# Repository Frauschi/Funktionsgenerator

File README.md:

# Funktionsgenerator

Dieses Repository beinhaltet alle relevaten Dateien für den Bau eines Funktionsgenerators. Dieser ist
im Rahmen einer Projektarbeit and der *Ostbayerischen Technischen Hochschule Regensburg* enstanden.

### Specs des Funktionsgenerators

- Zwei unabhängige Ausgangskanäle
- Signalformen: Sinus, Recheck (einstellbarer Duty-Cycle), Dreieck, Sägezahn (ansteigend und abfallend)
- Frequenz: 1Hz – 10MHz
- Ausgangsspannung: -10V – +10V 
- Signal-Offset: -5V – +5V
- Signal-Phase -180° – +180°

### Entwickler

- Manuel Dentgen
- Tobias Frauenschläger
- Thomas Taugenbeck

### Verzeichnisstruktur

- `Bilder` 
	
	Dieses Verzeichnis beinhaltet sowohl Bilder vom Gerät selbst (3D Modell und tatsächliches Gerät) als 
	auch Bilder von den erzeugten Signalen.
	
- `Dokumentation` 

	Dieser Ordner enthält zum einen die Projektdokumentation und zum anderen eine Bedienungsanleitung für den 
	fertigen Funktionsgenerator.
	
- `Hardware` 

	Hier sind alle Dateien für die drei entwickelten Platinen abgelegt (Schaltplan und Layout).
	
- `Software` 
	
	In diesem Verzeichnis ist die Firmware für den Mikrocontroller zu finden, der das ganze Gerät steuert.

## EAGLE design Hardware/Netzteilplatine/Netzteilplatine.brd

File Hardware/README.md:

# Hardware Funktionsgenerator

In diesem Verzeichnis ist die selbstentwickelte Hardware für den Funktionsgenerator zu finden, 
aufgeteilt auf die drei Platinen `Frontpanel`, `Hauptplatine` und `Netzteilplatine`. Im jeweiligen Ordner 
sind die Schaltplan- und Layout-Dateien abgelegt, wobei diese mit dem Programm 
[Eagle](https://www.autodesk.com/products/eagle/overview) in Version 7.7 erstellt wurden. Die Schaltpläne
sind zudem als PDF verfügbar.

## Dokumentation

Die Dokumentation der Hardware ist in der Projektdokumentation im Verzeichnis `Dokumentation` zu finden.

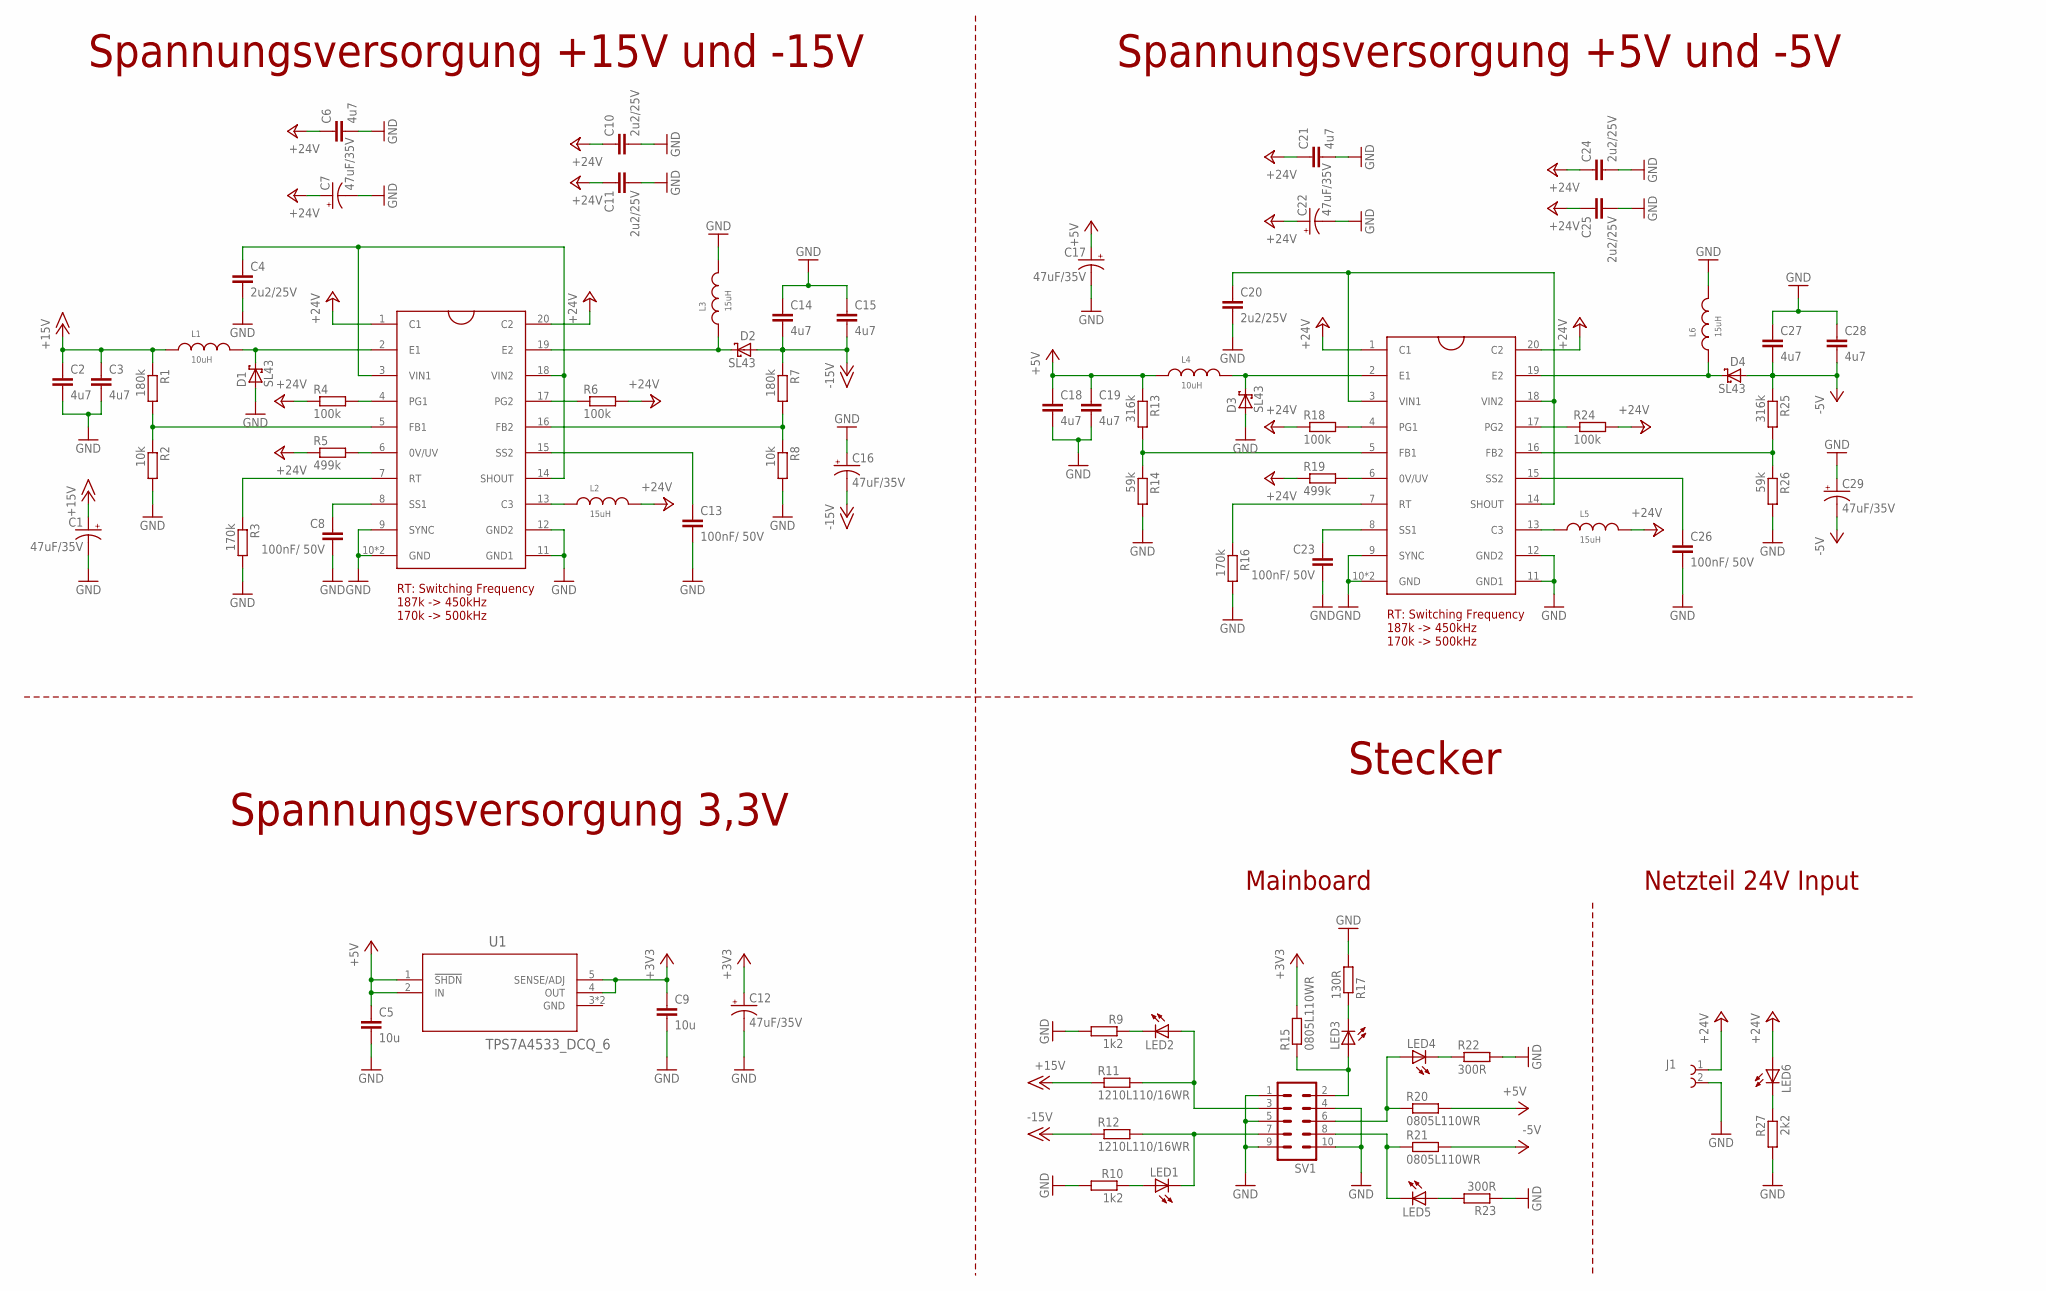
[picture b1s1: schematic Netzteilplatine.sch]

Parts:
C1, C7, C12, C16, C17, C22, C29: 47uF/35V; PANASONIC_D
C2, C3, C6, C14, C15, C18, C19, C21, C27, C28: 4u7; C1210
C4, C10, C11, C20, C24, C25: 2u2/25V; C1210
C5, C9: 10u; C0805
C8, C13, C23, C26: 100nF/ 50V; C0603
D1, D2, D3, D4: SL43; SMC
J1: 691137810002
L1, L4: 10uH; WE-PD_7332-7345_PLASTIC_BASE
L2, L3, L5, L6: 15uH; WE-PD2SR_7850
LED1, LED2, LED3, LED4, LED5, LED6: LEDCHIPLED_0603; CHIPLED_0603
R1, R7: 180k; R0603
R2, R8: 10k; R0603
R3, R16: 170k; R0603
R4, R6, R18, R24: 100k; R0603
R5, R19: 499k; R0603
R9, R10: 1k2; R0603
R11, R12: 1210L110/16WR; R1206
R13, R25: 316k; R0603
R14, R26: 59k; R0603
R15, R20, R21: 0805L110WR; R0805
R17: 130R; R0603
R22, R23: 300R; R0603
R27: 2k2; R0603
SV1: ML10
U1: TPS7A4533_DCQ_6; DCQ6
U2, U3: LT8471; TSSOP20

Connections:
+3V3: C9.1, C12.+, R15.2, U1.4 (OUT), U1.5 (SENSE/ADJ)
+5V: C5.1, C17.+, C18.1, C19.1, L4.1, R13.1, R20.2, U1.1 (!SHDN), U1.2 (IN)
+15V: C1.+, C2.1, C3.1, L1.1, R1.1, R11.1
+24V: C6.1, C7.+, C10.1, C11.1, C21.1, C22.+, C24.1, C25.1, J1.1, L2.2, L5.2, LED6.A, R4.1, R5.1, R6.2, R18.1, R19.1, R24.2, U2.1 (C1), U2.20 (C2), U3.1 (C1), U3.20 (C2)
-5V: C27.2, C28.2, C29.-, D4.A, R21.2, R25.1
-15V: C14.2, C15.2, C16.-, D2.A, R7.1, R12.1
GND: C1.-, C2.2, C3.2, C4.2, C5.2, C6.2, C7.-, C8.2, C9.2, C10.2, C11.2, C12.-, C13.2, C14.1, C15.1, C16.+, C17.-, C18.2, C19.2, C20.2, C21.2, C22.-, C23.2, C24.2, C25.2, C26.2, C27.1, C28.1, C29.+, D1.A, D3.A, J1.2, L3.2, L6.2, R2.2, R3.2, R8.2, R9.2, R10.2, R14.2, R16.2, R17.2, R22.2, R23.1, R26.2, R27.2, SV1.1, SV1.4, SV1.5, SV1.9, SV1.10, U1.3 (GND), U1.P$1 (GND), U2.9 (SYNC), U2.10 (GND), U2.11 (GND1), U2.12 (GND2), U2.P$1 (GND), U3.9 (SYNC), U3.10 (GND), U3.11 (GND1), U3.12 (GND2), U3.P$1 (GND)
unnamed: C4.1, U2.3 (VIN1), U2.14 (SHOUT), U2.18 (VIN2)
unnamed: R7.2, R8.1, U2.16 (FB2)
unnamed: R1.2, R2.1, U2.5 (FB1)
unnamed: R5.2, U2.6 (0V/UV)
unnamed: C20.1, U3.3 (VIN1), U3.14 (SHOUT), U3.18 (VIN2)
unnamed: C8.1, U2.8 (SS1)
unnamed: R19.2, U3.6 (0V/UV)
unnamed: C13.1, U2.15 (SS2)
unnamed: C23.1, U3.8 (SS1)
unnamed: C26.1, U3.15 (SS2)
unnamed: R25.2, R26.1, U3.16 (FB2)
unnamed: R13.2, R14.1, U3.5 (FB1)
unnamed: R3.1, U2.7 (RT)
unnamed: R16.1, U3.7 (RT)
unnamed: D1.C, L1.2, U2.2 (E1)
unnamed: D2.C, L3.1, U2.19 (E2)
unnamed: L2.1, U2.13 (C3)
unnamed: D3.C, L4.2, U3.2 (E1)
unnamed: R6.1, U2.17 (PG2)
unnamed: R4.2, U2.4 (PG1)
unnamed: D4.C, L6.1, U3.19 (E2)
unnamed: L5.1, U3.13 (C3)
unnamed: R24.1, U3.17 (PG2)
unnamed: R18.2, U3.4 (PG1)
unnamed: LED3.A, R15.1, SV1.2
unnamed: LED4.A, R20.1, SV1.6
unnamed: LED4.C, R22.1
unnamed: LED1.C, R12.2, SV1.7
unnamed: LED5.C, R21.1, SV1.8
unnamed: LED5.A, R23.2
unnamed: LED2.A, R11.2, SV1.3
unnamed: LED3.C, R17.1
unnamed: LED2.C, R9.1
unnamed: LED1.A, R10.1
unnamed: LED6.C, R27.1

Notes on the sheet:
Spannungsversorgung +15V und -15V
Spannungsversorgung 3,3V
RT: Switching Frequency 187k -> 450kHz 170k -> 500kHz
Spannungsversorgung +5V und -5V
Stecker
Mainboard
Netzteil 24V Input

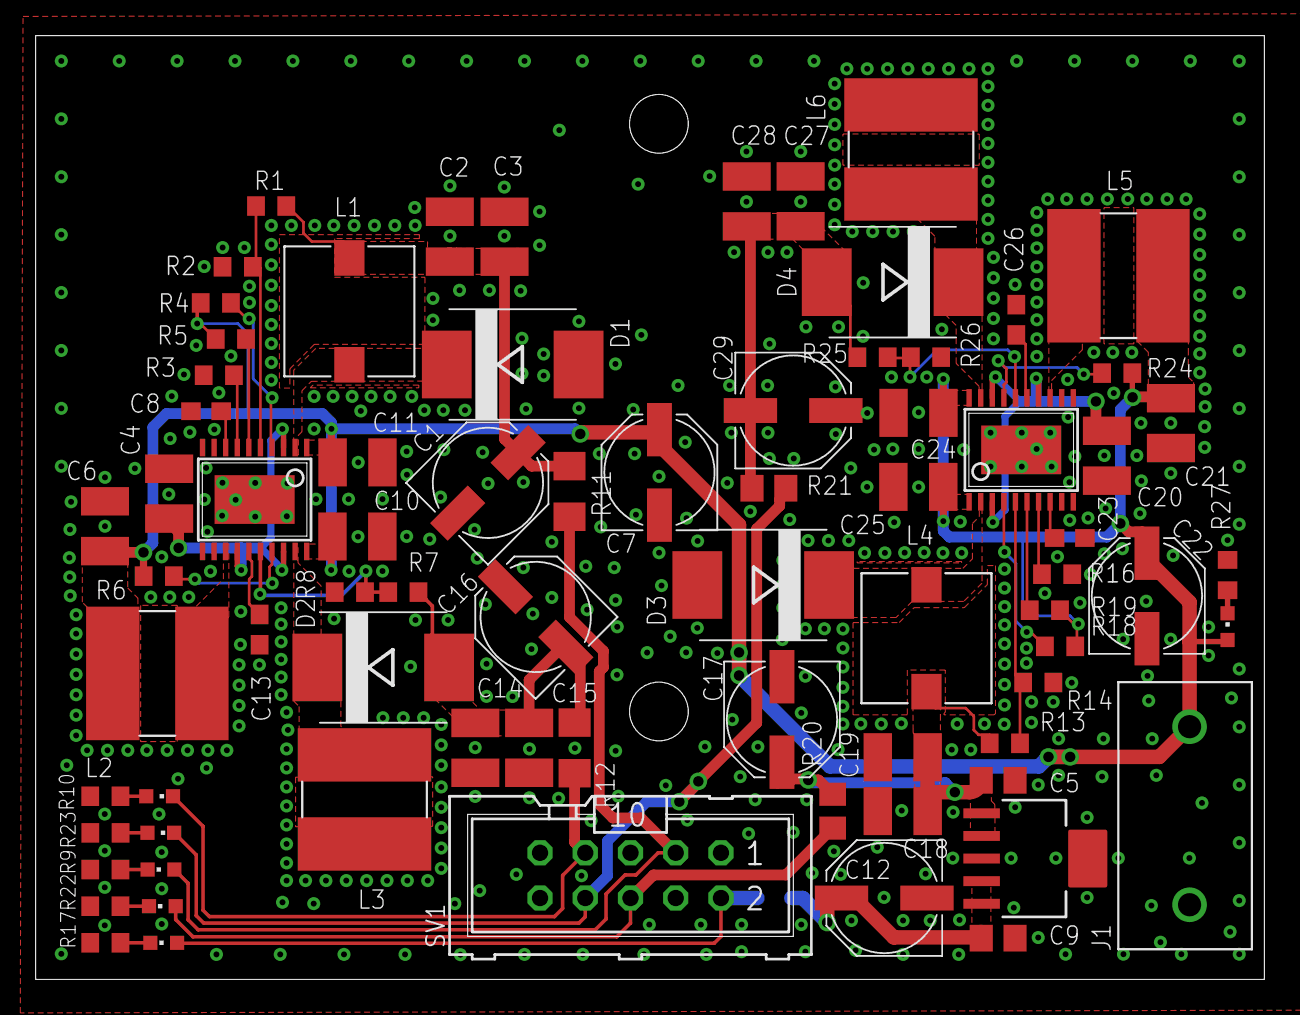
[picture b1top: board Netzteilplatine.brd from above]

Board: 2 copper layers, 69.0 x 53.0 mm, 77 parts (1 on the bottom side), 42 nets.

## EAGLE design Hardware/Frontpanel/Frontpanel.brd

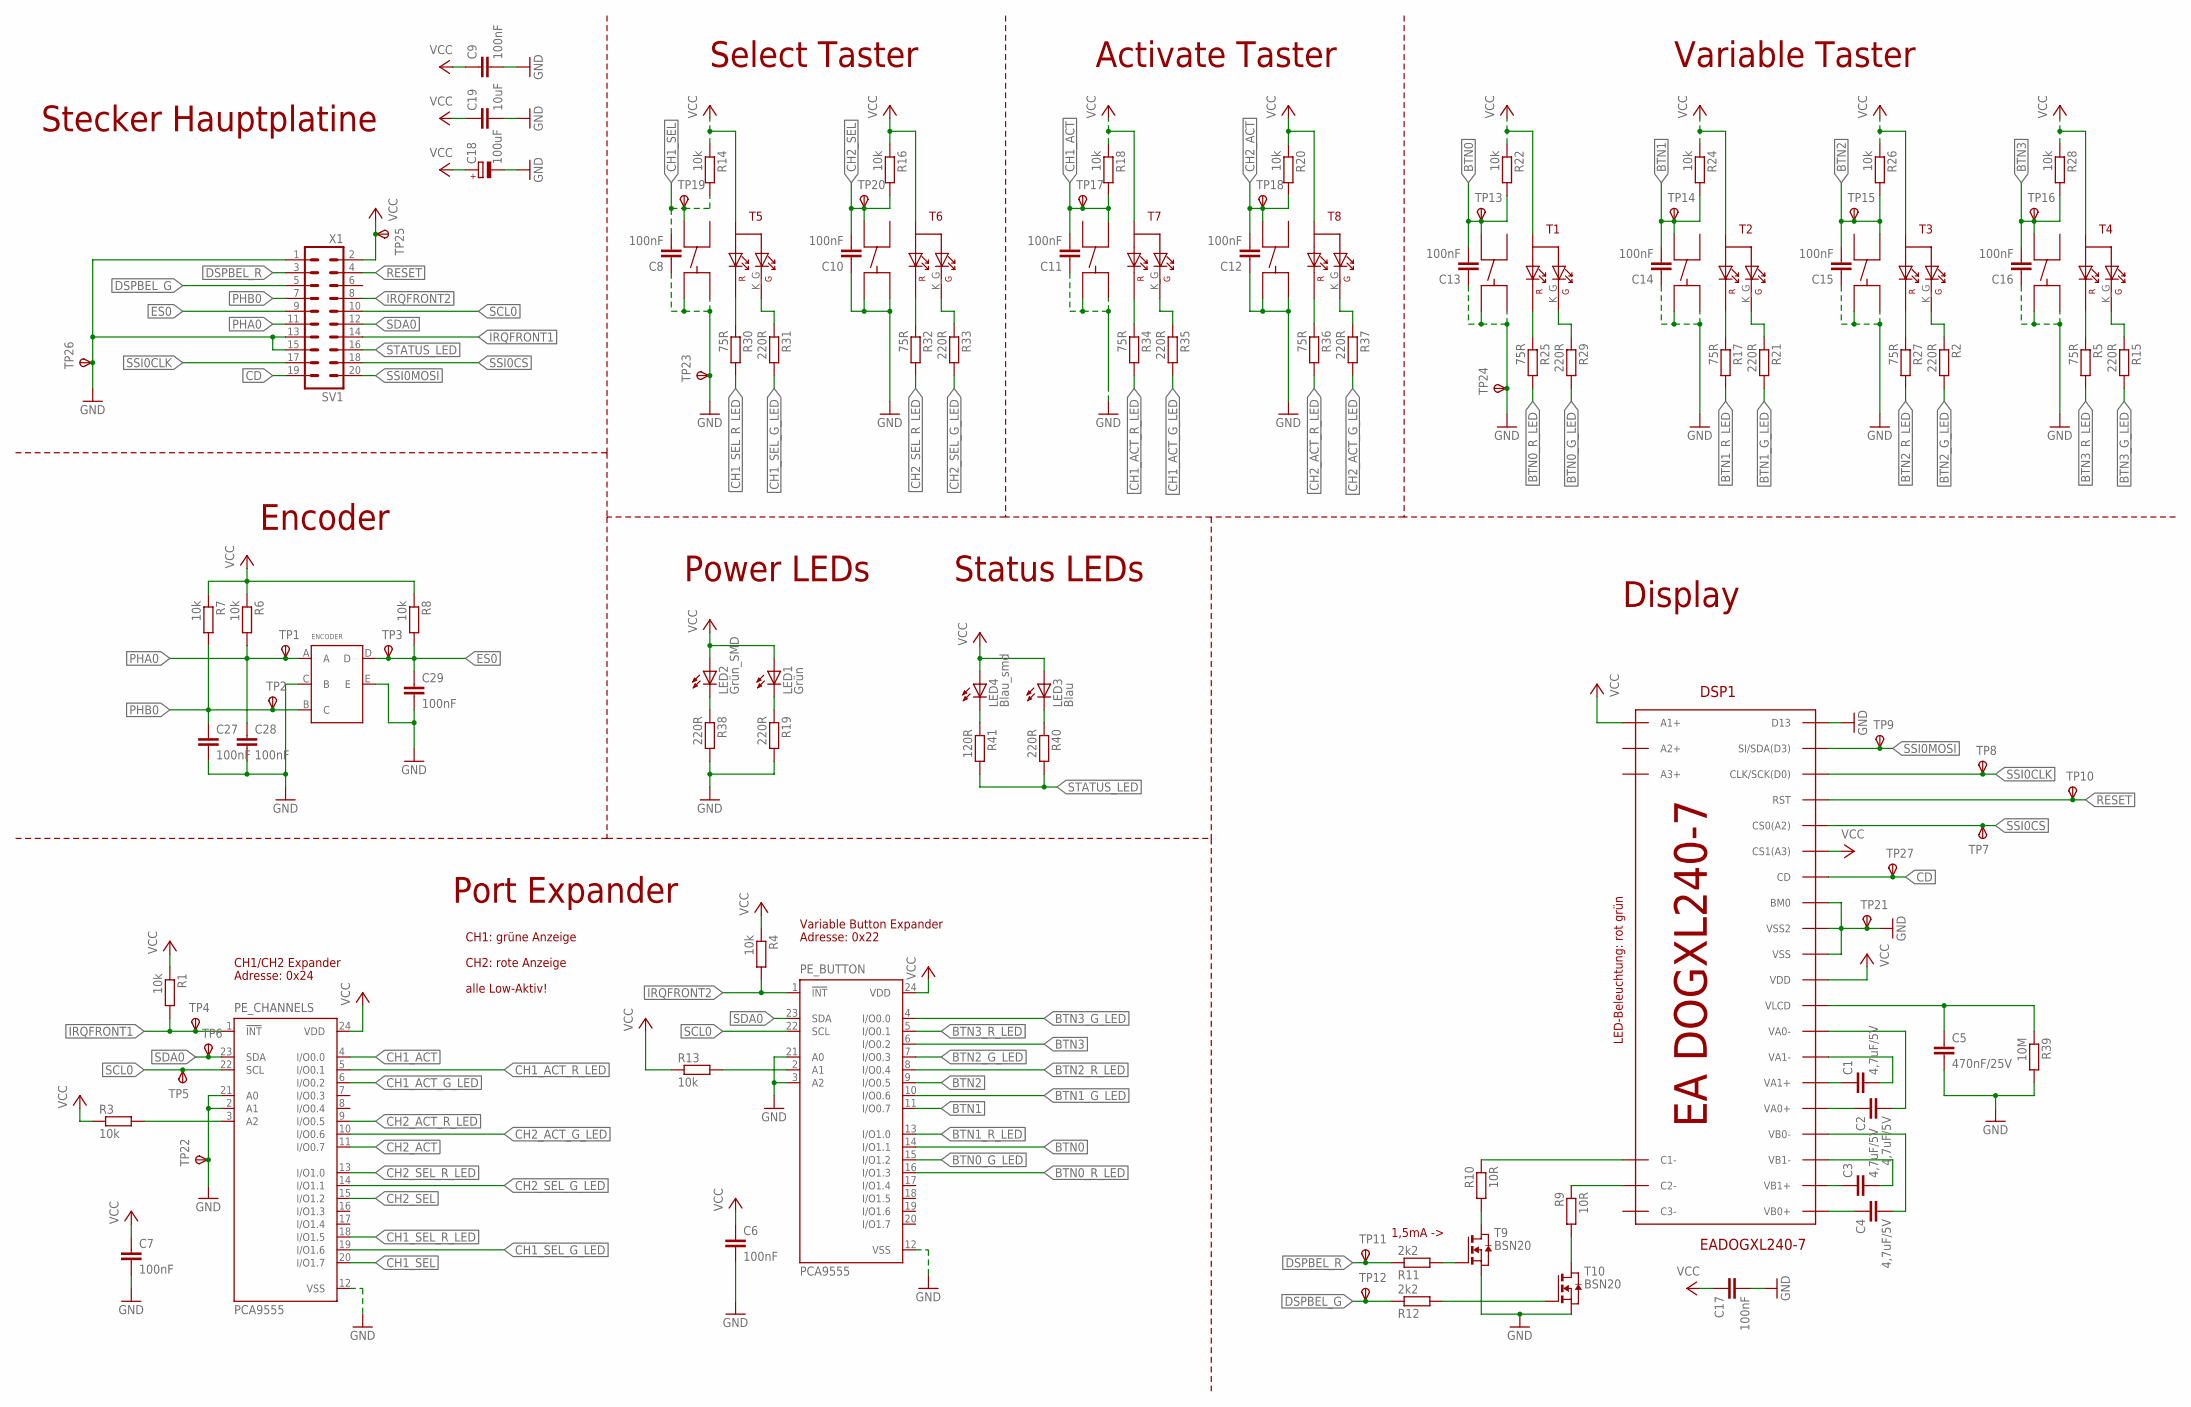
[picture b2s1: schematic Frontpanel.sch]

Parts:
C1, C2, C3, C4: 4,7uF/5V; C0805
C5: 470nF/25V; C0603
C6, C7, C8, C9, C10, C11, C12, C13, C14, C15, C16, C17, C27, C28, C29: 100nF; C0603
C18: 100uF; CT7343
C19: 10uF; C0805
DSP1: EADOGXL240-7
ENCODER: ENCODER
LED1: Grün; LED5MM
LED2: Grün_SMD; CHIP-LED0603
LED3: Blau; LED5MM
LED4: Blau_smd; CHIP-LED0603
PE_BUTTON: PCA9555; SSOP24_DBQ
PE_CHANNELS: PCA9555; SSOP24_DBQ
R1, R3, R4, R6, R7, R8, R13, R14, R16, R18, R20, R22, R24, R26, R28: 10k; R0603
R2, R15, R19, R21, R29, R31, R33, R35, R37, R38, R40: 220R; R0603
R5, R17, R25, R27, R30, R32, R34, R36: 75R; R0603
R9, R10: 10R; M1206
R11, R12: 2k2; R0603
R39: 10M; R0603
R41: 120R; R0603
SV1: X1; ML20
T1, T2, T3, T4, T5, T6, T7, T8: TASTER_2FSH9_E_BEL; TASTER_3FSH9_SMD_E
T9, T10: BSN20; SOT-23
TP1, TP2, TP3, TP4, TP5, TP6, TP7, TP8, TP9, TP10, TP11, TP12, TP13, TP14, TP15, TP16, TP17, TP18, TP19, TP20, TP21, TP22, TP23, TP24, TP25, TP26, TP27: TPSB1,27; B1,27

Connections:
BTN0: C13.2, PE_BUTTON.14 (I/O1.1), R22.2, T1.13, TP13.TP
BTN0_G_LED: PE_BUTTON.15 (I/O1.2), R29.2
BTN0_R_LED: PE_BUTTON.16 (I/O1.3), R25.2
BTN1: C14.2, PE_BUTTON.11 (I/O0.7), R24.2, T2.13, TP14.TP
BTN1_G_LED: PE_BUTTON.10 (I/O0.6), R21.2
BTN1_R_LED: PE_BUTTON.13 (I/O1.0), R17.2
BTN2: C15.2, PE_BUTTON.9 (I/O0.5), R26.2, T3.23, TP15.TP
BTN2_G_LED: PE_BUTTON.7 (I/O0.3), R2.2
BTN2_R_LED: PE_BUTTON.8 (I/O0.4), R27.2
BTN3: C16.2, PE_BUTTON.6 (I/O0.2), R28.2, T4.13, TP16.TP
BTN3_G_LED: PE_BUTTON.4 (I/O0.0), R15.2
BTN3_R_LED: PE_BUTTON.5 (I/O0.1), R5.2
CD: DSP1.CD, SV1.19, TP27.TP
CH1_ACT: C11.2, PE_CHANNELS.4 (I/O0.0), R18.2, T7.23, TP17.TP
CH1_ACT_G_LED: PE_CHANNELS.6 (I/O0.2), R35.2
CH1_ACT_R_LED: PE_CHANNELS.5 (I/O0.1), R34.2
CH1_SEL: C8.2, PE_CHANNELS.20 (I/O1.7), R14.2, T5.13, TP19.TP
CH1_SEL_G_LED: PE_CHANNELS.19 (I/O1.6), R31.2
CH1_SEL_R_LED: PE_CHANNELS.18 (I/O1.5), R30.2
CH2_ACT: C12.2, PE_CHANNELS.11 (I/O0.7), R20.2, T8.13, TP18.TP
CH2_ACT_G_LED: PE_CHANNELS.10 (I/O0.6), R37.2
CH2_ACT_R_LED: PE_CHANNELS.9 (I/O0.5), R36.2
CH2_SEL: C10.2, PE_CHANNELS.15 (I/O1.2), R16.2, T6.13, TP20.TP
CH2_SEL_G_LED: PE_CHANNELS.14 (I/O1.1), R33.2
CH2_SEL_R_LED: PE_CHANNELS.13 (I/O1.0), R32.2
DSPBEL_G: R12.1, SV1.5, TP12.TP
DSPBEL_R: R11.1, SV1.3, TP11.TP
ES0: C29.1, ENCODER.D, R8.2, SV1.9, TP3.TP
GND: C5.2, C6.2, C7.2, C8.1, C9.2, C10.1, C11.1, C12.1, C13.1, C14.1, C15.1, C16.1, C17.2, C18.-, C19.2, C27.2, C28.2, C29.2, DSP1.BM0, DSP1.D13, DSP1.VSS1 (VSS), DSP1.VSS2, ENCODER.C (B), ENCODER.E, PE_BUTTON.3 (A2), PE_BUTTON.12 (VSS), PE_BUTTON.21 (A0), PE_CHANNELS.2 (A1), PE_CHANNELS.12 (VSS), PE_CHANNELS.21 (A0), R19.2, R38.2, R39.2, SV1.1, SV1.13, SV1.15, T1.14, T1.24, T2.14, T2.24, T3.14, T3.24, T4.14, T4.24, T5.14, T5.24, T6.14, T6.24, T7.14, T7.24, T8.14, T8.24, T9.2 (S), T10.2 (S), TP21.TP, TP22.TP, TP23.TP, TP24.TP, TP26.TP
IRQFRONT1: PE_CHANNELS.1 (!INT), R1.2, SV1.14, TP4.TP
IRQFRONT2: PE_BUTTON.1 (!INT), R4.2, SV1.8
unnamed: PE_CHANNELS.3 (A2), R3.2
unnamed: R27.1, T3.K_R (KR)
unnamed: DSP1.C1-, R10.1
unnamed: PE_BUTTON.2 (A1), R13.2
unnamed: R11.2, T9.3 (G)
unnamed: DSP1.C2-, R9.1
unnamed: R12.2, T10.3 (G)
unnamed: R29.1, T1.K_G (KG)
unnamed: R25.1, T1.K_R (KR)
unnamed: R17.1, T2.K_R (KR)
unnamed: C1.1, DSP1.VA1+
unnamed: C2.1, DSP1.VA0+
unnamed: C3.1, DSP1.VB1+
unnamed: C4.1, DSP1.VB0+
unnamed: C3.2, DSP1.VB1-
unnamed: C4.2, DSP1.VB0-
unnamed: R9.2, T10.1 (D)
unnamed: R10.2, T9.1 (D)
unnamed: R21.1, T2.K_G (KG)
unnamed: R36.1, T8.K_R (KR)
unnamed: R2.1, T3.K_G (KG)
unnamed: R5.1, T4.K_R (KR)
unnamed: R15.1, T4.K_G (KG)
unnamed: R37.1, T8.K_G (KG)
unnamed: R34.1, T7.K_R (KR)
unnamed: R35.1, T7.K_G (KG)
unnamed: R32.1, T6.K_R (KR)
unnamed: R33.1, T6.K_G (KG)
unnamed: R30.1, T5.K_R (KR)
unnamed: R31.1, T5.K_G (KG)
unnamed: C1.2, DSP1.VA1-
unnamed: LED1.K (C), R19.1
unnamed: LED2.C, R38.1
unnamed: C2.2, DSP1.VA0-
unnamed: LED3.K (C), R40.1
unnamed: C5.1, DSP1.VLCD, R39.1
unnamed: LED4.C, R41.1
PHA0: C28.1, ENCODER.A, R6.2, SV1.11, TP1.TP
PHB0: C27.1, ENCODER.B (C), R7.2, SV1.7, TP2.TP
RESET: DSP1.RST, SV1.4, TP10.TP
SCL0: PE_BUTTON.22 (SCL), PE_CHANNELS.22 (SCL), SV1.10, TP5.TP
SDA0: PE_BUTTON.23 (SDA), PE_CHANNELS.23 (SDA), SV1.12, TP6.TP
SSI0CLK: DSP1.SCK(D0) (CLK/SCK(D0)), SV1.17, TP8.TP
SSI0CS: DSP1.CS0(A2), SV1.18, TP7.TP
SSI0MOSI: DSP1.SDA(D3) (SI/SDA(D3)), SV1.20, TP9.TP
STATUS_LED: R40.2, R41.2, SV1.16
VCC: C6.1, C7.1, C9.1, C17.1, C18.+, C19.1, DSP1.A1+, DSP1.CS1(A3), DSP1.VDD, LED1.A, LED2.A, LED3.A, LED4.A, PE_BUTTON.24 (VDD), PE_CHANNELS.24 (VDD), R1.1, R3.1, R4.1, R6.1, R7.1, R8.1, R13.1, R14.1, R16.1, R18.1, R20.1, R22.1, R24.1, R26.1, R28.1, SV1.2, T1.A, T2.A, T3.A, T4.A, T5.A, T6.A, T7.A, T8.A, TP25.TP

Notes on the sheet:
Stecker Hauptplatine
Adresse: 0x24
Encoder
Port Expander
Adresse: 0x22
CH1: grüne Anzeige
CH2: rote Anzeige
Variable Button Expander
CH1/CH2 Expander
alle Low-Aktiv!
Select Taster
Activate Taster
Variable Taster
Power LEDs
LED-Beleuchtung: rot grün
1,5mA ->
Status LEDs
Display

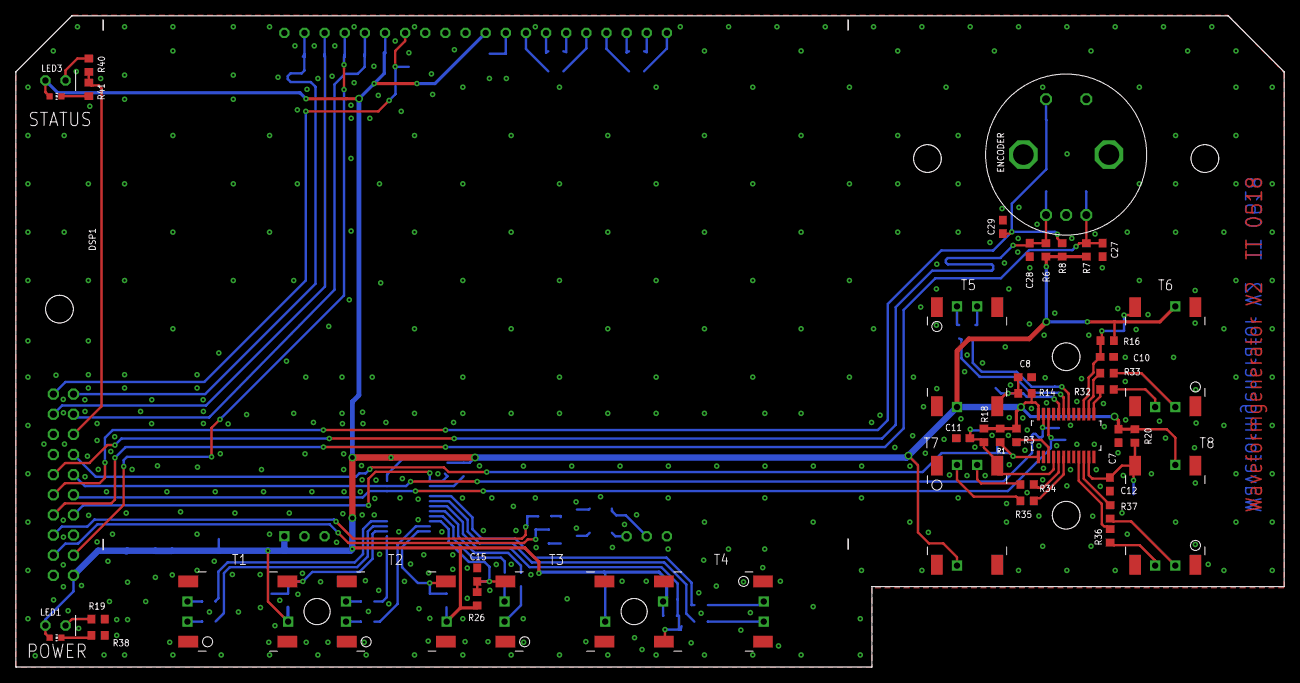
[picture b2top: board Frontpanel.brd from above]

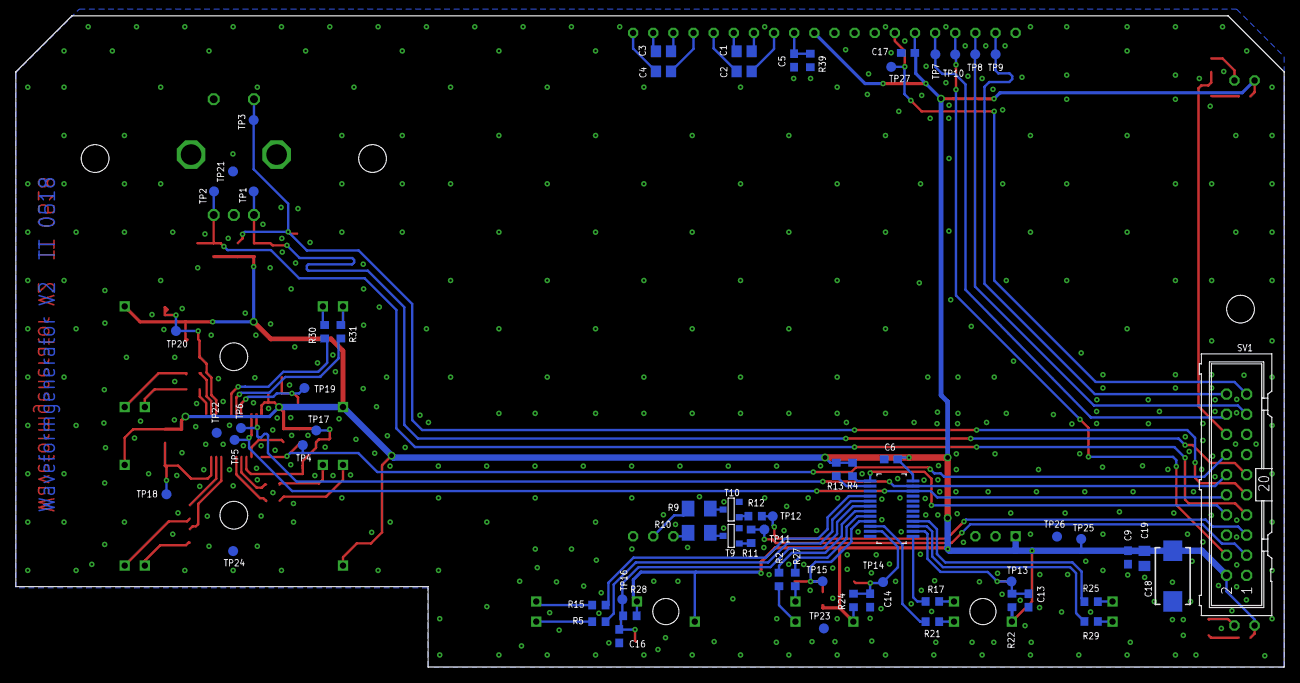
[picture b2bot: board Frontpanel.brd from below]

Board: 2 copper layers, 160.0 x 82.2 mm, 108 parts (64 on the bottom side), 78 nets.

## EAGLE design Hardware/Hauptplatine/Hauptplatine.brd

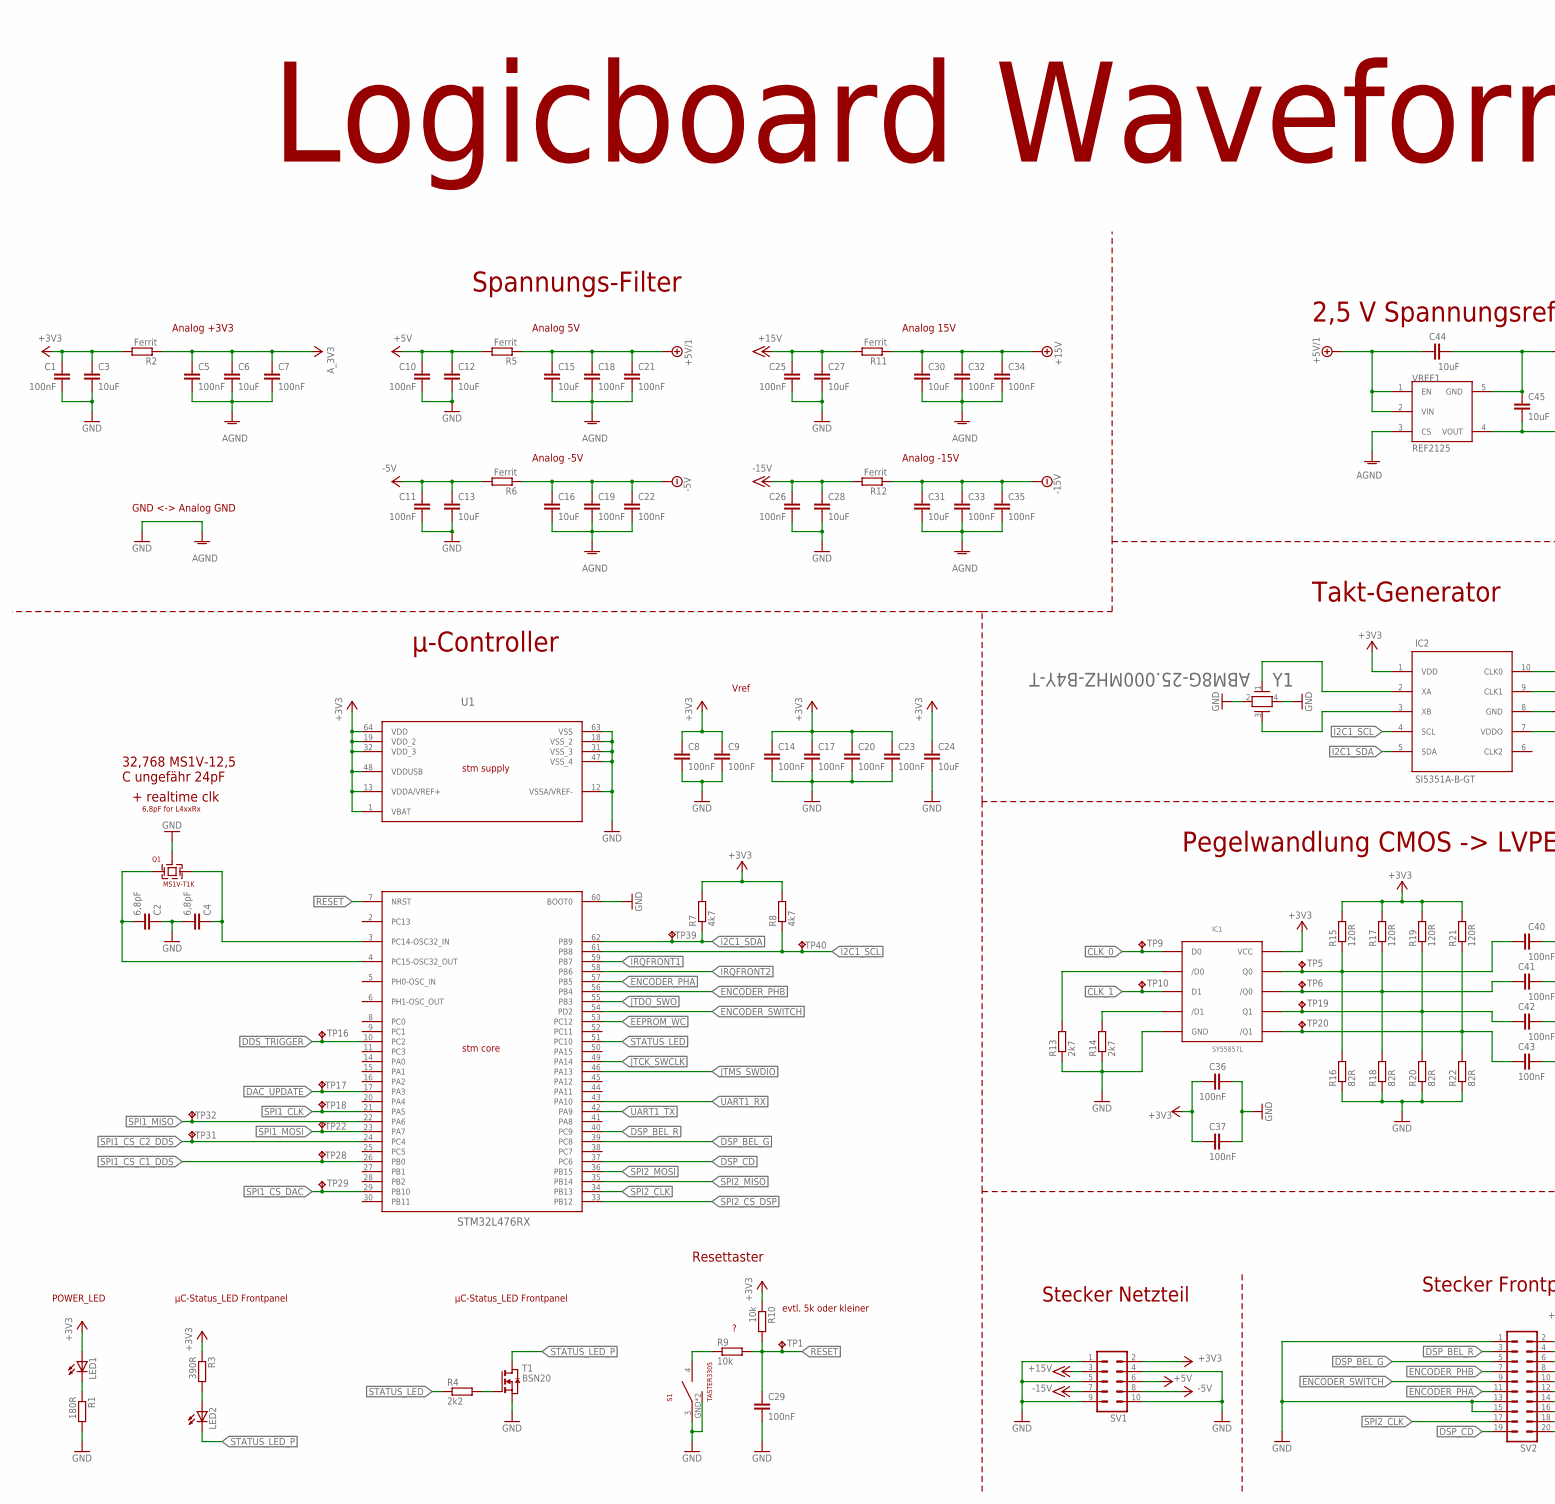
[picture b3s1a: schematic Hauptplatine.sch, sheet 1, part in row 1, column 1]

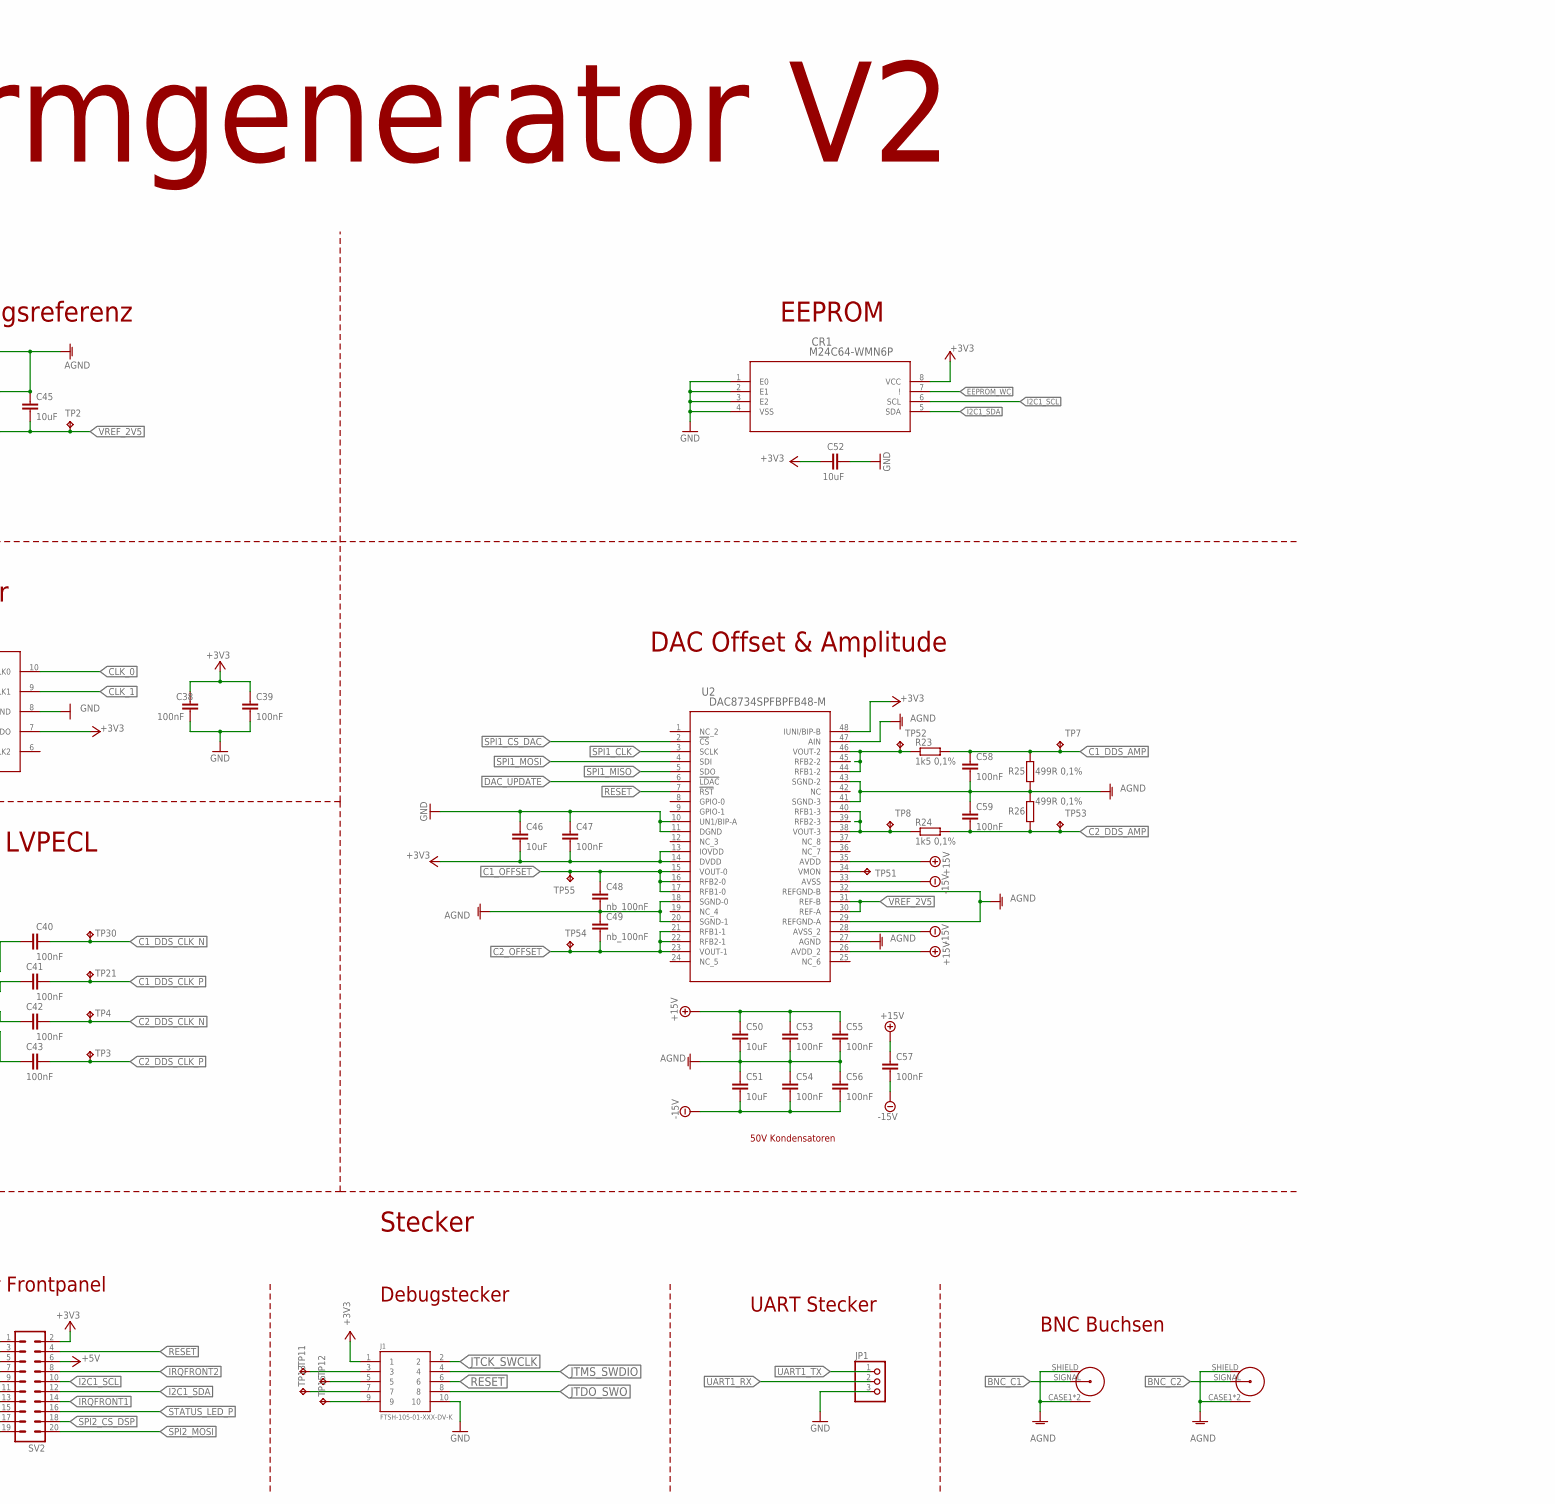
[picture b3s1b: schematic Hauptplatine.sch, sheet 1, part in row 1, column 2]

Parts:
C1, C5, C7, C8, C9, C10, C11, C14, C17, C18, C19, C20, C21, C22, C23, C25, C26, C29, C32, C33, C34, C35, C36, C37, C38, C39, C40, C41, C42, C43, C47, C53, C54, C55, C56, C57, C58, C59: 100nF; C0603
C2, C4: 6,8pF; C0603
C3, C6, C12, C13, C15, C16, C24, C27, C28, C30, C31, C44, C45, C46, C50, C51, C52: 10uF; C0603
C48, C49: nb_100nF; C0603
CR1: M24C64-WMN6P; SO-8
IC1: SY55857L; MSOP(K10-1)
IC2: SI5351A-B-GT; MSOP10
J1: FTSH-105-01-XXX-DV-K
JP1: PINHD-1X3; 1X03
LED1, LED2: LEDCHIPLED_0603; CHIPLED_0603
Q1: MS1V-T1K
R1: 180R; R0603
R2, R5, R6, R11, R12: Ferrit; R0603
R3: 390R; R0603
R4: 2k2; R0603
R7, R8: 4k7; R0603
R9, R10: 10k; R0603
R13, R14: 2k7; R0603
R15, R17, R19, R21: 120R; R0603
R16, R18, R20, R22: 82R; R0603
R23, R24: 1k5 0,1%; R0603
R25, R26: 499R 0,1%; R0603
S1: TASTER3305
SV1: ML10
SV2: ML20
T1: BSN20; SOT-23
TP1, TP2, TP3, TP4, TP5, TP6, TP7, TP8, TP9, TP10, TP11, TP12, TP13, TP15, TP16, TP17, TP18, TP19, TP20, TP21, TP22, TP28, TP29, TP30, TP31, TP32, TP39, TP40, TP51, TP52, TP53, TP54, TP55: TPB1,27; B1,27
U1: STM32L476RX; LQFP64-10X10MM
U2: DAC8734SPFBPFB48-M; PFB48-M
VREF1: REF2125; SOT23-5L
X1, X2: 740845_BNC
Y1: ABM8G-25.000MHZ-B4Y-T; CRYSTAL_ABM8G

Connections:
+3V3: C1.1, C3.1, C8.1, C9.1, C14.1, C17.1, C20.1, C23.1, C24.1, C36.1, C37.1, C38.1, C39.1, C46.2, C47.2, C52.1, CR1.8 (VCC), IC1.VCC, IC2.1 (VDD), IC2.7 (VDDO), J1.1, LED1.A, R2.2, R3.1, R7.2, R8.2, R10.1, R15.2, R17.2, R19.2, R21.2, SV1.2, SV2.2, U1.1 (VBAT), U1.13 (VDDA/VREF+), U1.19 (VDD_2), U1.32 (VDD_3), U1.48 (VDDUSB), U1.64 (VDD), U2.13 (IOVDD), U2.14 (DVDD), U2.48 (IUNI/BIP-B); also elsewhere on the board
+5V: C10.1, C12.1, R5.2, SV1.6, SV2.6
+5V/1: C15.1, C18.1, C21.1, C44.1, R5.1, VREF1.1 (EN), VREF1.2 (VIN); also elsewhere on the board
+15V: C25.1, C27.1, R11.2, SV1.3
+18V: C30.1, C32.1, C34.1, C50.1, C53.1, C55.1, C57.1, R11.1, U2.26 (AVDD_2), U2.35 (AVDD); also elsewhere on the board
-5V: C16.1, C19.1, C22.1, R6.1; also elsewhere on the board
-5V/D: C11.1, C13.1, R6.2, SV1.8
-15V: C26.1, C28.1, R12.2, SV1.7
-18V: C31.1, C33.1, C35.1, C51.2, C54.2, C56.2, C57.2, R12.1, U2.28 (AVSS_2), U2.33 (AVSS); also elsewhere on the board
ANALOG_3V3: C5.1, C6.1, C7.1, R2.1; also elsewhere on the board
BNC_C1: X1.SIGNAL; also elsewhere on the board
BNC_C2: X2.SIGNAL; also elsewhere on the board
C1_DDS_AMP: C58.1, R23.2, R25.2, TP7.TP; also elsewhere on the board
C1_DDS_CLK_N: C40.1, TP30.TP; also elsewhere on the board
C1_DDS_CLK_P: C41.1, TP21.TP; also elsewhere on the board
C1_OFFSET: C48.1, TP55.TP, U2.15 (VOUT-0), U2.16 (RFB2-0), U2.17 (RFB1-0); also elsewhere on the board
C2_DDS_AMP: C59.2, R24.2, R26.1, TP53.TP; also elsewhere on the board
C2_DDS_CLK_N: C42.1, TP4.TP; also elsewhere on the board
C2_DDS_CLK_P: C43.1, TP3.TP; also elsewhere on the board
C2_OFFSET: C49.2, TP54.TP, U2.21 (RFB1-1), U2.22 (RFB2-1), U2.23 (VOUT-1); also elsewhere on the board
CLK_0: IC1.D0, IC2.10 (CLK0), TP9.TP
CLK_1: IC1.D1, IC2.9 (CLK1), TP10.TP
DAC_UPDATE: TP17.TP, U1.17 (PA3), U2.6 (!LDAC)
DDS_TRIGGER: TP16.TP, U1.10 (PC2); also elsewhere on the board
DSP_BEL_G: SV2.5, U1.39 (PC8)
DSP_BEL_R: SV2.3, U1.40 (PC9)
DSP_CD: SV2.19, U1.37 (PC6)
EEPROM_WC: CR1.7 (!), U1.53 (PC12)
ENCODER_PHA: SV2.11, U1.57 (PB5)
ENCODER_PHB: SV2.7, U1.56 (PB4)
ENCODER_SWITCH: SV2.9, U1.54 (PD2)
GND: C1.2, C2.1, C3.2, C4.2, C5.2, C6.2, C7.2, C8.2, C9.2, C10.2, C11.2, C12.2, C13.2, C14.2, C15.2, C16.2, C17.2, C18.2, C19.2, C20.2, C21.2, C22.2, C23.2, C24.2, C25.2, C26.2, C27.2, C28.2, C29.2, C30.2, C31.2, C32.2, C33.2, C34.2, C35.2, C36.2, C37.2, C38.2, C39.2, C44.2, C45.1, C46.1, C47.1, C48.2, C49.1, C50.2, C51.1, C52.2, C53.2, C54.1, C55.2, C56.1, C58.2, C59.1, CR1.1 (E0), CR1.2 (E1), CR1.3 (E2), CR1.4 (VSS), IC1.GND, IC2.8 (GND), J1.10, JP1.3, Q1.GND, R1.2, R13.1, R14.1, R16.1, R18.1, R20.1, R22.1, R25.1, R26.2, S1.3, S1.GND, S1.GND2 (GND), SV1.1, SV1.4, SV1.5, SV1.9, SV1.10, SV2.1, SV2.13, SV2.15, T1.2 (S), U1.12 (VSSA/VREF-), U1.18 (VSS_2), U1.31 (VSS_3), U1.47 (VSS_4), U1.60 (BOOT0), U1.63 (VSS), U2.10 (UN1/BIP-A), U2.11 (DGND), U2.18 (SGND-0), U2.20 (SGND-1), U2.27 (AGND), U2.29 (REFGND-A), U2.32 (REFGND-B), U2.41 (SGND-3), U2.43 (SGND-2), U2.47 (AIN), VREF1.3 (CS), VREF1.5 (GND), X1.CASE1 (CASE), X1.CASE2 (CASE), X1.SHIELD, X2.CASE1 (CASE), X2.CASE2 (CASE), X2.SHIELD, Y1.2, Y1.4; also elsewhere on the board
I2C1_SCL: CR1.6 (SCL), IC2.4 (SCL), R8.1, SV2.10, TP40.TP, U1.61 (PB8)
I2C1_SDA: CR1.5 (SDA), IC2.5 (SDA), R7.1, SV2.12, TP39.TP, U1.62 (PB9)
IRQFRONT1: SV2.14, U1.59 (PB7)
IRQFRONT2: SV2.8, U1.58 (PB6)
JTCK_SWCLK: J1.2, U1.49 (PA14)
JTDO_SWO: J1.8, U1.55 (PB3)
JTMS_SWDIO: J1.4, U1.46 (PA13)
unnamed: R9.1, S1.4
unnamed: LED1.C, R1.1
unnamed: R23.1, TP52.TP, U2.44 (RFB1-2), U2.45 (RFB2-2), U2.46 (VOUT-2)
unnamed: IC2.2 (XA), Y1.1
unnamed: IC2.3 (XB), Y1.3
unnamed: J1.3, TP11.TP
unnamed: R24.1, TP8.TP, U2.38 (VOUT-3), U2.39 (RFB2-3), U2.40 (RFB1-3)
unnamed: C2.2, Q1.1, U1.4 (PC15-OSC32_OUT)
unnamed: R4.2, T1.3 (G)
unnamed: LED2.A, R3.2
unnamed: J1.5, TP12.TP
unnamed: J1.7, TP13.TP
unnamed: IC1./D1, R14.2
unnamed: IC1./D0, R13.2
unnamed: C40.2, IC1.Q0, R15.1, R16.2, TP5.TP
unnamed: C41.2, IC1./Q0, R17.1, R18.2, TP6.TP
unnamed: C42.2, IC1.Q1, R19.1, R20.2, TP19.TP
unnamed: J1.9, TP15.TP
unnamed: C43.2, IC1./Q1, R21.1, R22.2, TP20.TP
unnamed: TP51.TP, U2.34 (VMON)
unnamed: C4.1, Q1.2, U1.3 (PC14-OSC32_IN)
RESET: C29.1, J1.6, R9.2, R10.2, SV2.4, TP1.TP, U1.7 (NRST), U2.7 (!RST); also elsewhere on the board
SPI1_CLK: TP18.TP, U1.21 (PA5), U2.3 (SCLK); also elsewhere on the board
SPI1_CS_C1_DDS: TP28.TP, U1.26 (PB0); also elsewhere on the board
SPI1_CS_C2_DDS: TP31.TP, U1.24 (PC4); also elsewhere on the board
SPI1_CS_DAC: TP29.TP, U1.29 (PB10), U2.2 (!CS)
SPI1_MISO: TP32.TP, U1.22 (PA6), U2.5 (SDO); also elsewhere on the board
SPI1_MOSI: TP22.TP, U1.23 (PA7), U2.4 (SDI); also elsewhere on the board
SPI2_CLK: SV2.17, U1.34 (PB13)
SPI2_CS_DSP: SV2.18, U1.33 (PB12)
SPI2_MISO: U1.35 (PB14)
SPI2_MOSI: SV2.20, U1.36 (PB15)
STATUS_LED: R4.1, U1.51 (PC10)
STATUS_LED_P: LED2.C, SV2.16, T1.1 (D)
UART1_RX: JP1.2, U1.43 (PA10)
UART1_TX: JP1.1, U1.42 (PA9)
VREF_2V5: C45.2, TP2.TP, U2.30 (REF-A), U2.31 (REF-B), VREF1.4 (VOUT)

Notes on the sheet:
Stecker Frontpanel
Debugstecker
Stecker
Spannungs-Filter
Analog -5V
Analog +3V3
Analog 5V
Analog -15V
Analog 15V
+ realtime clk
32,768 MS1V-12,5 C ungefähr 24pF
Logicboard Waveformgenerator V2
Resettaster
evtl. 5k oder kleiner
Stecker Netzteil
POWER_LED
µC-Status_LED Frontpanel
BNC Buchsen
6,8pF for L4xxRx
Vref
2,5 V Spannungsreferenz
Takt-Generator
µ-Controller
EEPROM
DAC Offset & Amplitude
50V Kondensatoren
UART Stecker
Pegelwandlung CMOS -> LVPECL
GND <-> Analog GND

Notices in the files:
parts and their libraries:
PowerMagnetics: Copyright: Würth Elektronik
